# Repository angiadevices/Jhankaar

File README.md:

# Jhankaar

झंकार | Jhankaar: The sound of chimes or percussion / The name of a popular series of remix cassettes in India in the 90s.

Update 16/11/25:

- From Toadstool Tech on the schematic, "The way the input detect probe is designed to work is that the GPIO send out a binary signal that is detected by the MCU when nothing is connected to the jack.
The way this works uses the switch pin on the standard mono thonkiconn jack.
The switch pin is connected to the output of the input detect GPIO, which then connects to the input of the ADC if nothing is plugged in.
When a cable is inserted though, this breaks that normalled connection and CV is received as normal.
So your INPUT_DETECT net should connect to the "Ring" of your jack instead of the tip.
There's actually a Kicad footprint for this normalled jack, called "AudioJack2_Switch" I think, which better repreents it, since you're not using a TRS stereo jack." </br>
- Replacing the W25Q128JVSIQ for W25Q32JVSSIQ did something! Able to navigate with the Mode button with LEDs now reflecting the changes in mode. Still no audio output yet, and most other I/O still seems to do nothing with preliminary testing.

Original:

An inexact hardware clone of the ['Ectocore' Eurorack module by Toadstool Tech and Infinite Digits](https://github.com/schollz/_core), Jhankaar currently stands as an incomplete project, the troubleshooting of which may currently be out of my capability/circumstances. [As the original schematics are provided under CC-BY-SA license](https://github.com/schollz/_core/blob/main/schematics/ectocore_v1.0.1.pdf), so too are the files in this repository.

The following hardware bugs have been confirmed to exist in this particular iteration of the files:
- R7 needs to be 10k, **NOT** 0R
- U22 10V shunt needs to be **flipped** (it is used for generating -10V in this circuit)

However, **fixing those changes on prototypes have not made the module functional.** They have gotten this design to the point of having power as and where expected, and flashing the module with the Ectocore firmware successfully, but actually turning on the module still results in a big pile of nothing.

I am hoping that members of the vibrant open-source synth DIY community more knowledgable than I can see mistakes here that I can't, and that this can serve as the basis for a triumphant encore of the Ectocore.

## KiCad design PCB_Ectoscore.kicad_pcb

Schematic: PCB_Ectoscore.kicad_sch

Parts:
C1, C2, C10, C11, C13, C14, C15, C16, C17, C19, C20, C22, C24, C25, C26, C30, C31, C32, C35, C36, C37, C40, C42, C45, C46, C47, C49, C51, C52, C53, C54, C55, C56, C57, C58, C59, C60, C61, C62, C63, C64, C65, C66, C67, C68, C71, C72, C73, C74, C75, C76, C77: 100nF; C_0603_1608Metric_Pad1.08x0.95mm_HandSolder; Manufacturer Part CC0603KRX7R9BB104
C3, C12: 1uF; CP_Elec_4x5.4; Manufacturer Part CA45-A025K105T
C4, C9: 10uF; C_0805_2012Metric; Manufacturer Part GRM21BR61H106KE43L
C5, C6, C48, C50, C69: 10uF; CP_Elec_6.3x5.4; Manufacturer Part RVT1H100M0605
C7, C8: 15pF; C_0603_1608Metric_Pad1.08x0.95mm_HandSolder; Manufacturer Part CC0603KRNPO9BN150
C21, C23: 1uF; C_0603_1608Metric_Pad1.08x0.95mm_HandSolder; Manufacturer Part CC0603KRX7R9BB105
C34, C44, C78, C79, C80: 100pF; C_0603_1608Metric_Pad1.08x0.95mm_HandSolder; Manufacturer Part CC0603KRX7R9BB101
C38, C39: 2.2uF; C_0603_1608Metric_Pad1.08x0.95mm_HandSolder; Manufacturer Part GRM188Z71E225KE43D
C41, C43: 1nF; C_0603_1608Metric_Pad1.08x0.95mm_HandSolder; Manufacturer Part CC0603KRX7R9BB102
C70: 22uF; CP_Elec_6.3x5.4; Manufacturer Part RVT1H220M0605
D1, D2, D3, D24: 1N5819WS; D_SOD-323_HandSoldering; Manufacturer Part 1N5819WS
D5, D6, D7, D8, D9, D10, D11, D12, D13, D14, D15, D16, D17, D18, D19, D20, D21, D22: WS2812B-2020; LED_WS2812B-2020_PLCC4_2.0x2.0mm; Manufacturer Part WS2812B-2020
J1: Conn_02x05_Odd_Even; IDC-Header_2x05_P2.54mm_Vertical; Manufacturer Part ZX-IDC2.54-2-5PZZ
J2: Conn_01x03; PinHeader_1x03_P2.54mm_Vertical; Manufacturer Part PZ254-1-03-Z-8.5
J3, J5, J6, J7, J8, J9, J10, J11: PJ-301M-3-B; Jack_3.5mm_QingPu_WQP-PJ398SM_Vertical; Manufacturer Part PJ-301M-3-B
J12: PJS008U-3000-0; PJS008U30000; Manufacturer_Part_Number PJS008U-3000-0; Mouser Part Number 945-PJS008U-3000-0
J13, J14: Conn_01x03; HDR-TH_3P-P2.54-V-M-1; Manufacturer Part PZ254-1-03-Z-8.5
LED1, LED2, LED3, LED4, LED5, LED6: LED-0603_R; LED0603-R-RD_RED; Part Number PCM5100AQPWRQ1
Q1: MMBT3904; SOT-23; Manufacturer Part MMBT3904LT1G
R1, R2, R5, R29, R36, R42, R47, R50, R57, R58, R64, R81, R82, R83: 1kΩ; R_0603_1608Metric_Pad0.98x0.95mm_HandSolder; Manufacturer Part 0603WAF1001T5E
R3, R4, R8, R52, R55, R71: 10kΩ; R_0603_1608Metric_Pad0.98x0.95mm_HandSolder; Manufacturer Part 0603WAF1002T5E
R6, R9: 1k; R_0603_1608Metric_Pad0.98x0.95mm_HandSolder; Manufacturer Part 0603WAF1001T5E
R7: 0R; R_0603_1608Metric_Pad0.98x0.95mm_HandSolder; Manufacturer Part 0603WAF0000T5E
R10, R15, R68, R69, R70: 10kΩ; POT_TH_Alps_RK09K_Single_Vertical; Manufacturer Part RK09K1130A8G
R27, R28: 27; R_0603_1608Metric_Pad0.98x0.95mm_HandSolder; Manufacturer Part 0603WAF270JT5E
R48, R49: 5.1kΩ; R_0603_1608Metric_Pad0.98x0.95mm_HandSolder; Manufacturer Part 0603WAF5101T5E
R51, R54, R65: 2.2kΩ; R_0603_1608Metric_Pad0.98x0.95mm_HandSolder; Manufacturer Part 0603WAF2201T5E
R53, R56, R72, R77, R80: 33kΩ; R_0603_1608Metric_Pad0.98x0.95mm_HandSolder; Manufacturer Part 0603WAF3302T5E
R59: 200Ω; R_0603_1608Metric_Pad0.98x0.95mm_HandSolder; Manufacturer Part 0603WAF2000T5E
R60, R62: 18kΩ; R_0603_1608Metric_Pad0.98x0.95mm_HandSolder; Manufacturer Part 0603WAF1802T5E
R61, R63: 9.1kΩ; R_0603_1608Metric_Pad0.98x0.95mm_HandSolder; Manufacturer Part 0603WAF9101T5E
R66, R67, R73, R76, R79: 100kΩ; R_0603_1608Metric_Pad0.98x0.95mm_HandSolder; Manufacturer Part 0603WAF1003T5E
R74, R75, R78: 200kΩ; R_0603_1608Metric_Pad0.98x0.95mm_HandSolder; Manufacturer Part 0603WAF2003T5E
SW1, SW2, SW3: TL1105SPF100Q; KEY-TH_4P-L6.0-W6.0-P4.50-LS7.5; Manufacturer Part TL1105SPF100Q
SW4: ML6-H2T2BQA; SW-TH_ML6-H2XX; Manufacturer Part ML6-H2T2BQA
SW5, SW6: SW_Push; SW_SPST_CK_RS282G05A3; Manufacturer Part RS282G05A3SM
TP1, TP2, TP3, TP4, TP5, TP6, TP7, TP8: TestPoint; TestPoint_Pad_D1.5mm; Manufacturer Part N/A; not fitted
U1: L7805; TO-252-2; Manufacturer Part L7805CDT-TR
U2: NCP1117-3.3_SOT223; SOT-223-3_TabPin2; Manufacturer Part NCP1117ST33T3G
U7: W25Q128JVS; SOIC-8_5.3x5.3mm_P1.27mm; Manufacturer Part W25Q128JVSIQ
U11: RP2040; RP2040-QFN-56; Manufacturer Part RP2040
U15: 12402012E212A; USB-SMD_TYPE-C16PIN-1; Manufacturer Part 12402012E212A; LCSC Part C5150972
U16: PCM5100AQPWRQ1; TSSOP-20_4.4x6.5mm_P0.65mm; Manufacturer Part PCM5100AQPWRQ1
U17, U18: TL072HIDR; SOIC-8_3.9x4.9mm_P1.27mm; Manufacturer Part TL072HIDR
U19: TLP2361(TPL,E(T; SO-5-6_4.55x3.7mm_P1.27mm; Manufacturer Part TLP2361(TPL,E(T
U20: MCP3208T-CI/SL; SOIC-16_3.9x9.9mm_P1.27mm; Manufacturer Part MCP3208T-CI/SL
U21: MCP1804x-5002xMB; SOT-89-3; Manufacturer Part MCP1804T-5002I/MB
U22: LM4040DIM3-10.0/NOPB; SOT-23; Manufacturer Part LM4040DIM3-10.0/NOPB
U23: MCP6004T-I/ST; TSSOP-14_4.4x5mm_P0.65mm; Manufacturer Part MCP6004T-I/ST
Y1: ABM8-272-T3; Crystal_SMD_3225-4Pin_3.2x2.5mm; Manufacturer Part ABM8-272-T3

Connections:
3.3V: C9.1, C12.1, C15.1, C22.1, C23.1, C24.1, C25.1, C26.1, C30.1, C31.1, C32.1, C42.2, C49.2, C50.1, C51.2, C52.2, C53.2, C54.2, C55.2, C56.2, C57.2, C58.2, C59.2, C60.2, C61.2, C62.2, C63.2, C64.2, C65.2, C66.2, C67.2, C68.2, D5.4 (VDD), D6.4 (VDD), D7.4 (VDD), D8.4 (VDD), D9.4 (VDD), D10.4 (VDD), D11.4 (VDD), D12.4 (VDD), D13.4 (VDD), D14.4 (VDD), D15.4 (VDD), D16.4 (VDD), D17.4 (VDD), D18.4 (VDD), D19.4 (VDD), D20.4 (VDD), D21.4 (VDD), D22.4 (VDD), J12.4 (VDD), R3.2, R4.2, R7.1, R8.2, R42.1, R47.1, R67.2, R81.1, R82.1, R83.2, TP2.1, U2.2 (VO), U7.8 (VCC), U11.1 (IOVDD), U11.10 (IOVDD), U11.22 (IOVDD), U11.33 (IOVDD), U11.42 (IOVDD), U11.43 (ADC_AVDD), U11.44 (VREG_IN), U11.48 (USB_VDD), U11.49 (IOVDD), U16.11 (FLT), U16.17 (XSMT), U16.20 (DVDD), U19.6 (VDD)
5V: C3.1, D1.2 (A), TP3.1, U1.3 (OUT)
10NEG: C71.2, R65.2, R74.2, R75.2, R78.2, U22.1 (K)
12POS: C10.2, C13.2, C46.2, C47.2, C70.1, D2.1 (K), TP4.1, U1.1 (IN), U17.8 (V+), U18.8 (V+), U21.3 (IN)
+1V1: C19.1, C20.1, C21.1, U11.23 (DVDD), U11.45 (VREG_VOUT), U11.50 (DVDD)
+3V3_A: C17.2, C35.2, C36.2, C48.1, C69.1, C77.2, R10.1, R15.1, R68.1, R69.1, R70.1, TP7.1, U16.1 (CPVDD), U16.8 (AVDD), U20.15 (Vref), U20.16 (Vdd), U21.1 (OUT), U23.4 (V+)
-12V: C11.1, C14.1, C40.2, C45.2, D3.2 (A), R65.1, TP5.1, U17.4 (V-), U18.4 (V-)
/QSPI_SCLK: U7.6 (CLK), U11.52 (QSPI_SCLK)
/QSPI_SD0: U7.5 (DI(IO0)), U11.53 (QSPI_SD0)
/QSPI_SD1: U7.2 (DO(IO1)), U11.55 (QSPI_SD1)
/QSPI_SD2: U7.3 (IO2), U11.54 (QSPI_SD2)
/QSPI_SD3: U7.7 (IO3), U11.51 (QSPI_SD3)
/QSPI_SS: R6.1, R7.2, U7.1 (~CS), U11.56 (QSPI_SS)
/RUN: SW6.2, U11.26 (RUN)
/SWCLK: J13.1, U11.24 (SWCLK)
/SWD: J13.2, U11.25 (SWD)
/USB_D+: R27.1, U15.A6 (D+), U15.B6 (D+)
/USB_D-: R28.1, U15.A7 (D-), U15.B7 (D-)
/XIN: C7.1, U11.20 (XIN), Y1.1
/XOUT: R9.1, U11.21 (XOUT)
/~USB_BOOT: R6.2, SW5.2
ADC_CSN: U11.12 (GPIO9), U20.10 (~CS/SHDN)
ADC_RX: U11.11 (GPIO8), U20.12 (Dout)
ADC_SCLK: U11.13 (GPIO10), U20.13 (CLK)
ADC_TX: U11.14 (GPIO11), U20.11 (Din)
BTN_BANK: C16.2, R5.2, R8.1, U11.31 (GPIO20)
BTN_MODE: C1.2, R1.2, R3.1, U11.2 (GPIO0)
BTN_MULT: C2.2, R2.2, R4.1, U11.3 (GPIO1)
BTN_TAP_TEMPO: SW4.1, SW4.2, U11.4 (GPIO2)
CLOCK_IN: Q1.3 (C), R67.1, U11.17 (GPIO14)
CLOCK_OUT: R29.1, U11.30 (GPIO19), U18.3 (+)
CV_AMEN: C80.1, R80.1, U20.3 (CH2), U23.14
CV_BREAK: C79.1, R77.1, U20.6 (CH5), U23.8
CV_SAMPLE: C78.1, R72.1, U20.8 (CH7), U23.7
DAC_BCK: U11.32 (GPIO21), U16.13 (BCK)
DAC_DIN: U11.35 (GPIO23), U16.14 (DIN)
DAC_LRCK: U11.34 (GPIO22), U16.15 (LRCK)
DAC_OUTL: R51.2, U16.6 (OUTL)
DAC_OUTR: R54.2, U16.7 (OUTR)
GND: C1.1, C2.1, C3.2, C4.2, C5.2, C6.1, C7.2, C8.2, C9.2, C10.1, C11.2, C12.2, C13.1, C14.2, C15.2, C16.1, C17.1, C19.2, C20.2, C21.2, C22.2, C23.2, C24.2, C25.2, C26.2, C30.2, C31.2, C32.2, C35.1, C36.1, C37.1, C39.1, C40.1, C41.1, C42.1, C43.1, C45.1, C46.1, C47.1, C48.2, C49.1, C50.2, C51.1, C52.1, C53.1, C54.1, C55.1, C56.1, C57.1, C58.1, C59.1, C60.1, C61.1, C62.1, C63.1, C64.1, C65.1, C66.1, C67.1, C68.1, C69.2, C70.2, C71.1, C72.1, C73.1, C74.1, C75.1, C76.1, C77.1, D5.2 (VSS), D6.2 (VSS), D7.2 (VSS), D8.2 (VSS), D9.2 (VSS), D10.2 (VSS), D11.2 (VSS), D12.2 (VSS), D13.2 (VSS), D14.2 (VSS), D15.2 (VSS), D16.2 (VSS), D17.2 (VSS), D18.2 (VSS), D19.2 (VSS), D20.2 (VSS), D21.2 (VSS), D22.2 (VSS), J1.3, J1.4, J1.5, J1.6, J1.7, J1.8, J2.3, J3.S, J5.S, J6.S, J7.S, J8.S, J9.S, J10.S, J11.S, J12.6 (VSS), J12.MH1, J12.MH2, J13.3, J14.3, LED1.2 (C), LED2.2 (C), Q1.2 (E), R10.3, R15.3, R48.1, R49.1, R60.1, R62.1, R68.3, R69.3, R70.3, SW1.1, SW1.2, SW2.1, SW2.2, SW3.1, SW3.2, SW4.3, SW4.4, SW5.1, SW6.1, TP1.1, TP6.1, TP8.1, U1.2 (GND), U2.1 (GND), U7.4 (GND), U11.19 (TESTEN), U11.57 (GND), U15.17, U15.18, U15.19, U15.20, U15.A1B12 (GND), U15.B1A12 (GND), U16.3 (CPGND), U16.9 (AGND), U16.10 (DEMP), U16.12 (SCK), U16.16 (FMT), U16.19 (DGND), U17.3 (+), U17.5 (+), U19.4 (GND), U20.9 (DGND), U20.14 (AGND), U21.2 (GND), U22.2 (A), U23.5 (+), U23.10 (+), U23.11 (V-), U23.12 (+), Y1.2, Y1.4
INPUT_DETECT: J9.T, J10.T, J11.T, R71.1, R73.2, R76.2, R79.2
INPUT_DETECT_UNBUFFER: U11.27 (GPIO16), U23.3 (+)
KNOB_AMEN: C76.2, R70.2, U20.1 (CH0)
KNOB_AMEN_ATTEN: C75.2, R69.2, U20.2 (CH1)
KNOB_BREAK: C74.2, R68.2, U20.4 (CH3)
KNOB_GRIMOIRE: C73.2, R10.2, U20.5 (CH4)
KNOB_SAMPLE: C72.2, R15.2, U20.7 (CH6)
LED_MODE1: LED3.2 (C), U11.8 (GPIO6)
LED_MODE2: LED4.2 (C), U11.15 (GPIO12)
LED_MODE3: LED6.2 (C), U11.28 (GPIO17)
LED_MODE4: LED5.2 (C), U11.16 (GPIO13)
LED_TAP_TEMPO: SW4.L2, U11.5 (GPIO3)
MIDI: U11.18 (GPIO15), U19.5 (VO)
unnamed: C8.1, R9.2, Y1.3
unnamed: C34.1, R50.1, R53.1, U17.1
unnamed: C41.2, R51.1, R52.2
unnamed: C43.2, R54.1, R55.2
unnamed: C44.1, R56.1, R57.1, U17.7
unnamed: C4.1, D1.1 (K), D24.1 (K), U2.3 (VI)
unnamed: C5.1, D2.2 (A), J1.9, J1.10
unnamed: C6.2, D3.1 (K), J1.1, J1.2
unnamed: D5.1 (DOUT), D6.3 (DIN)
unnamed: D6.1 (DOUT), D7.3 (DIN)
unnamed: D7.1 (DOUT), D8.3 (DIN)
unnamed: D8.1 (DOUT), D9.3 (DIN)
unnamed: D9.1 (DOUT), D10.3 (DIN)
unnamed: D10.1 (DOUT), D11.3 (DIN)
unnamed: D11.1 (DOUT), D12.3 (DIN)
unnamed: D12.1 (DOUT), D13.3 (DIN)
unnamed: D13.1 (DOUT), D14.3 (DIN)
unnamed: D14.1 (DOUT), D15.3 (DIN)
unnamed: D15.1 (DOUT), D16.3 (DIN)
unnamed: D16.1 (DOUT), D17.3 (DIN)
unnamed: D17.1 (DOUT), D18.3 (DIN)
unnamed: D18.1 (DOUT), D19.3 (DIN)
unnamed: D19.1 (DOUT), D20.3 (DIN)
unnamed: D20.1 (DOUT), D21.3 (DIN)
unnamed: D21.1 (DOUT), D22.3 (DIN)
unnamed: J2.1, U19.3 (K)
unnamed: J2.2, R59.1
unnamed: J3.T, R58.2
unnamed: J5.T, R50.2
unnamed: J6.T, R57.2
unnamed: J7.T, R64.2
unnamed: J8.T, R66.2
unnamed: LED1.1 (A), R29.2
unnamed: LED2.1 (A), R36.2
unnamed: LED3.1 (A), R42.2
unnamed: LED4.1 (A), R47.2
unnamed: LED5.1 (A), R81.2
unnamed: LED6.1 (A), R82.2
unnamed: Q1.1 (B), R66.1
unnamed: R1.1, SW1.3, SW1.4
unnamed: R2.1, SW2.3, SW2.4
unnamed: R5.1, SW3.3, SW3.4
unnamed: R48.2, U15.A5 (CC1)
unnamed: R49.2, U15.B5 (CC1)
unnamed: R58.1, R61.2, U18.1
unnamed: R63.2, R64.1, U18.7
unnamed: R83.1, SW4.L1
unnamed: R28.2, U11.46 (USB_DM)
unnamed: R27.2, U11.47 (USB_DP)
unnamed: C38.1, U16.4 (CAPM)
unnamed: C38.2, U16.2 (CAPP)
unnamed: C37.2, U16.18 (LDOO)
unnamed: C39.2, U16.5 (VNEG)
unnamed: C34.2, R52.1, R53.2, U17.2 (-)
unnamed: C44.2, R55.1, R56.2, U17.6 (-)
unnamed: R60.2, R61.1, U18.2 (-)
unnamed: R62.2, R63.1, U18.6 (-)
unnamed: R59.2, U19.1 (A)
unnamed: R71.2, U23.1, U23.2 (-)
unnamed: C78.2, R72.2, R73.1, R74.1, U23.6 (-)
unnamed: C79.2, R75.1, R76.1, R77.2, U23.9 (-)
unnamed: C80.2, R78.1, R79.1, R80.2, U23.13 (-)
SCL: J14.2, U11.7 (GPIO5)
SDA: J14.1, U11.6 (GPIO4)
SD_CMD: J12.3 (CMD), U11.37 (GPIO25)
SD_DAT0: J12.7 (DAT0), U11.38 (GPIO26_ADC0)
SD_DAT1: J12.8 (DAT1), U11.39 (GPIO27_ADC1)
SD_DAT2: J12.1 (DAT2), U11.40 (GPIO28_ADC2)
SD_DAT3: J12.2 (DAT3/CD), U11.41 (GPIO29_ADC3)
SD_SCLK: J12.5 (CLK), U11.36 (GPIO24)
TRIG_OUT: R36.1, U11.29 (GPIO18), U18.5 (+)
VBUS: D24.2 (A), U15.A4B9 (VBUS), U15.B4A9 (VBUS)
WS2812: D5.3 (DIN), U11.9 (GPIO7)

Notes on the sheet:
Thonkiconn
Shunt Voltage Reference IC Fixed 10V V ±1% 15 mA
Audio Stereo DAC with 32-bit, 384kHz PCM Interface
Make sure R3 and R4 are close to RP2040
LED RGB WS2812
SAMPLE
Crystal
CLOCK OUT
PJ-301M-3-B
SD CARD
OUT_R
AMEN
Flash
OUT_L
USB TYPE C
Eurorack Power In
RP2040
BREAK
Make sure C10 is close to pin 44 of RP2040
ADC
MIDI (optional)
Power
CLOCK IN
Buttons
Make sure C8 is close to pin 45 of RP2040
TRIG OUT

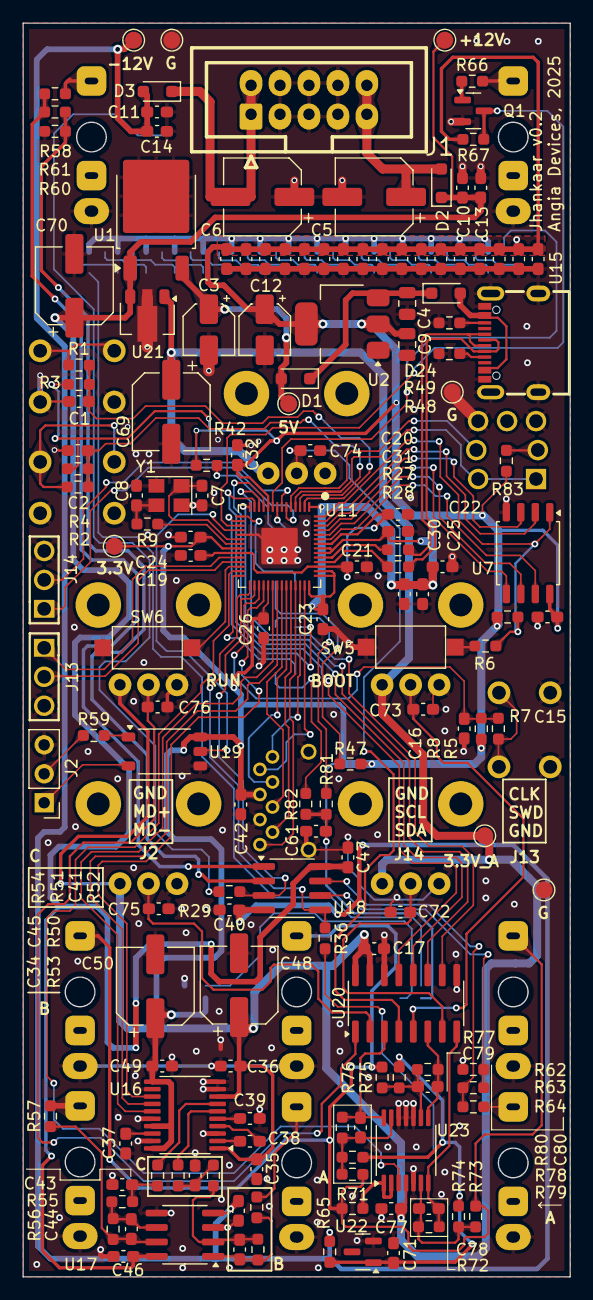
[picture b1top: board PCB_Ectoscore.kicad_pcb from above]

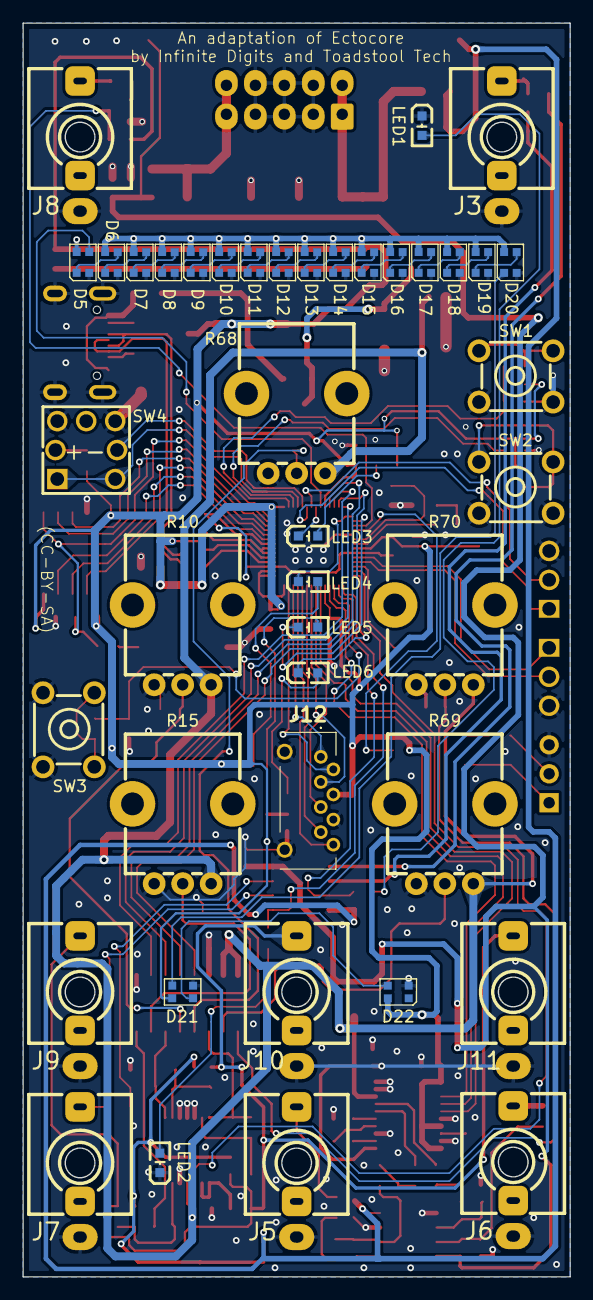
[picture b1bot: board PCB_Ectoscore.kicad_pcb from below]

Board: 2 copper layers, 48.0 x 110.0 mm, 198 parts (42 on the bottom side), 126 nets.
